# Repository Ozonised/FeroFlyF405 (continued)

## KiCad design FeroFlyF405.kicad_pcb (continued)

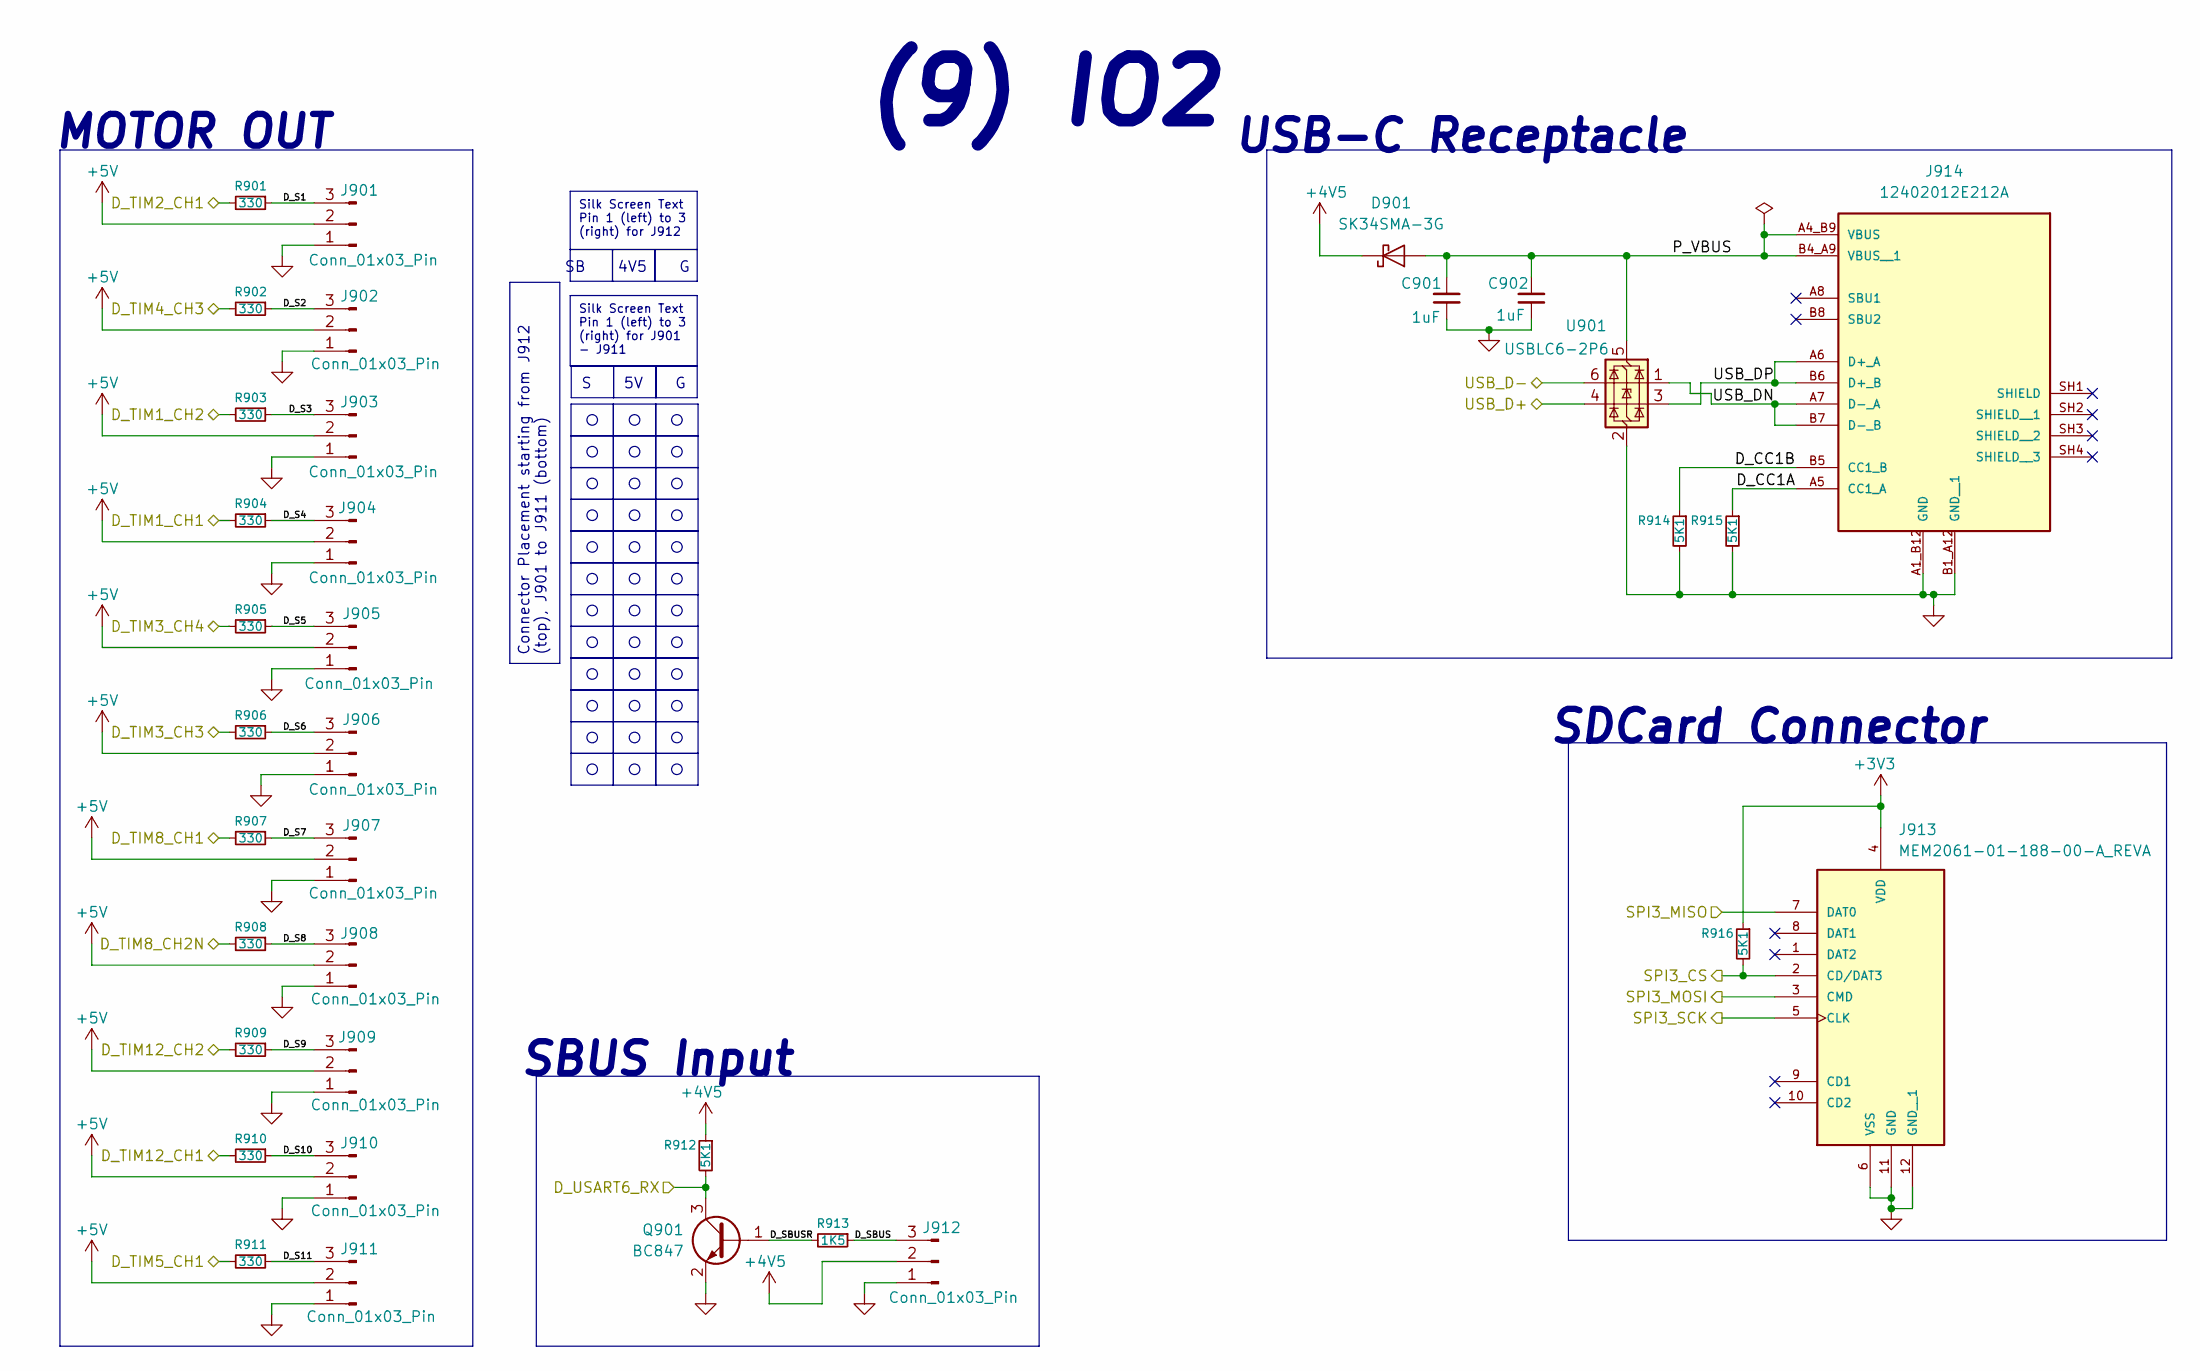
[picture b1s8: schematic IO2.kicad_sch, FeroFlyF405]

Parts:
C901, C902: 1uF; C_0603_1608Metric_Pad1.08x0.95mm_HandSolder; MPN C1608X7R1V105K080AC
D901: SK34SMA-3G; D_SMA; MPN SK34SMA-3G
J901, J902, J903, J904, J905, J906, J907, J908, J909, J910, J911, J912: Conn_01x03_Pin; PinHeader_1x03_P2.54mm_Vertical
J913: MEM2061-01-188-00-A_REVA; GCT_MEM2061-01-188-00-A_REVA
J914: 12402012E212A; AMPHENOL_12402012E212A; PARTREV 4
Q901: BC847; SOT-23; MPN BC847
R901, R902, R903, R904, R905, R906, R907, R908, R909, R910, R911: 330; R_0603_1608Metric_Pad0.98x0.95mm_HandSolder; MPN CR0603-FX-3300ELF
R912, R914, R915, R916: 5K1; R_0603_1608Metric_Pad0.98x0.95mm_HandSolder; MPN CR0603-FX-5101ELF
R913: 1K5; R_0603_1608Metric_Pad0.98x0.95mm_HandSolder; MPN CR0603-FX-3300ELF
U901: USBLC6-2P6; SOT-666; MPN USBLC6-2P6

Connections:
+3V3: J913.4 (VDD), R916.1; also elsewhere on the board
+4V5: D901.1 (K), J912.2, R912.1; also elsewhere on the board
+5V: J901.2, J902.2, J903.2, J904.2, J905.2, J906.2, J907.2, J908.2, J909.2, J910.2, J911.2; also elsewhere on the board
/IO/D_TIM1_CH1: R904.2; also elsewhere on the board
/IO/D_TIM1_CH2: R903.2; also elsewhere on the board
/IO/D_TIM2_CH1: R901.2; also elsewhere on the board
/IO/D_TIM3_CH3: R906.2; also elsewhere on the board
/IO/D_TIM3_CH4: R905.2; also elsewhere on the board
/IO/D_TIM4_CH3: R902.2; also elsewhere on the board
/IO/D_TIM5_CH1: R911.2; also elsewhere on the board
/IO/D_TIM8_CH1: R907.2; also elsewhere on the board
/IO/D_TIM8_CH2N: R908.2; also elsewhere on the board
/IO/D_TIM12_CH1: R910.2; also elsewhere on the board
/IO/D_TIM12_CH2: R909.2; also elsewhere on the board
/IO/D_USART6_RX: Q901.3 (C), R912.2; also elsewhere on the board
/IO/IO2/D_CC1A: J914.A5 (CC1_A), R915.1
/IO/IO2/D_CC1B: J914.B5 (CC1_B), R914.1
/IO/IO2/D_S1: J901.3, R901.1
/IO/IO2/D_S2: J902.3, R902.1
/IO/IO2/D_S3: J903.3, R903.1
/IO/IO2/D_S4: J904.3, R904.1
/IO/IO2/D_S5: J905.3, R905.1
/IO/IO2/D_S6: J906.3, R906.1
/IO/IO2/D_S7: J907.3, R907.1
/IO/IO2/D_S8: J908.3, R908.1
/IO/IO2/D_S9: J909.3, R909.1
/IO/IO2/D_S10: J910.3, R910.1
/IO/IO2/D_S11: J911.3, R911.1
/IO/IO2/D_SBUS: J912.3, R913.1
/IO/IO2/D_SBUSR: Q901.1 (B), R913.2
/IO/IO2/P_VBUS: C901.1, C902.1, D901.2 (A), J914.A4_B9 (VBUS), J914.B4_A9 (VBUS__1), U901.5 (VBUS)
/IO/IO2/USB_DN: J914.A7 (D-_A), J914.B7 (D-_B), U901.1 (I/O1)
/IO/IO2/USB_DP: J914.A6 (D+_A), J914.B6 (D+_B), U901.3 (I/O2)
/IO/SPI3_CS: J913.2 (CD/DAT3), R916.2; also elsewhere on the board
/IO/SPI3_MISO: J913.7 (DAT0); also elsewhere on the board
/IO/SPI3_MOSI: J913.3 (CMD); also elsewhere on the board
/IO/SPI3_SCK: J913.5 (CLK); also elsewhere on the board
/IO/USB_D+: U901.4 (I/O2); also elsewhere on the board
/IO/USB_D-: U901.6 (I/O1); also elsewhere on the board
GND: C901.2, C902.2, J901.1, J902.1, J903.1, J904.1, J905.1, J906.1, J907.1, J908.1, J909.1, J910.1, J911.1, J912.1, J913.6 (VSS), J913.11 (GND), J913.12 (GND__1), J914.A1_B12 (GND), J914.B1_A12 (GND__1), Q901.2 (E), R914.2, R915.2, U901.2 (GND); also elsewhere on the board

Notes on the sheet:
MOTOR OUT
S 5V G
USB-C Receptacle
SDCard Connector
SBUS Input
SB 4V5 G
(9) IO2
Silk Screen Text Pin 1 (left) to 3 (right) for J912
Silk Screen Text Pin 1 (left) to 3 (right) for J901 - J911
Connector Placement starting from J912 (top), J901 to J911 (bottom)

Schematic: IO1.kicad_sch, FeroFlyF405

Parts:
C801, C803, C805: 2.2uF; C_0805_2012Metric; MPN GCM21BR71C225KA64L
C802: 1uF; C_0603_1608Metric_Pad1.08x0.95mm_HandSolder; MPN C1608X7R1V105K080AC
C804: 0.1uF; C_0603_1608Metric_Pad1.08x0.95mm_HandSolder; MPN C1608X5R1H104K080AA
J801, J805: SM06B-GHS-TB(LF)(SN); JST_GH_SM06B-GHS-TB_1x06-1MP_P1.25mm_Horizontal; MPN JST_GH_SM06B-GHS-TB
J802, J804: SM04B-GHS-TB(LF)(SN); JST_GH_SM04B-GHS-TB_1x04-1MP_P1.25mm_Horizontal; MPN SM04B-GHS-TB(LF)(SN)
J803: SM03B-GHS-TB(LF)(SN); JST_GH_SM03B-GHS-TB_1x03-1MP_P1.25mm_Horizontal; MPN SM03B-GHS-TB(LF)(SN)
J806: Conn_01x02_MountingPin; Hirose_DF13C_CL535-0402-2-51_1x02-1MP_P1.25mm_Vertical
Q801: BC847; SOT-23; MPN BC847
R801: 10K; R_0603_1608Metric_Pad0.98x0.95mm_HandSolder; MPN CR0603-FX-1002ELF
R803: 1K5; R_0603_1608Metric_Pad0.98x0.95mm_HandSolder; MPN CR0603-FX-3300ELF
TP801, TP802, TP803, TP804, TP805, TP806, TP807, TP808, TP809, TP810, TP811, TP812, TP813, TP814, TP815, TP816: TestPoint; TestPoint_Pad_1.0x1.0mm

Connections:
+4V5: C801.1, C802.1, C803.1, J801.1, J802.1, J804.1, TP801.1 (1_1), TP802.1 (1_1); also elsewhere on the board
+5V: C805.1, J803.1, J805.1, J806.1, TP811.1 (1_1), TP815.1 (1_1); also elsewhere on the board
/IO/D_ADC1_CH10: C804.1, R801.1; also elsewhere on the board
/IO/D_BUZZER: R803.1; also elsewhere on the board
/IO/D_I2C1_SCL: J801.4, J804.2, TP806.1 (1_1); also elsewhere on the board
/IO/D_I2C1_SDA: J801.5, J804.3, TP810.1 (1_1); also elsewhere on the board
/IO/D_USART2_RX: J805.3, TP813.1 (1_1); also elsewhere on the board
/IO/D_USART2_TX: J805.2, TP812.1 (1_1); also elsewhere on the board
/IO/D_USART4_RX: J802.3, TP807.1 (1_1); also elsewhere on the board
/IO/D_USART4_TX: J802.2, TP804.1 (1_1); also elsewhere on the board
/IO/D_USART5_RX: J801.3, TP805.1 (1_1); also elsewhere on the board
/IO/D_USART5_TX: J801.2, TP803.1 (1_1); also elsewhere on the board
/IO/IO1/D_BUZ-: J806.2, Q801.3 (C), TP816.1 (1_1)
/IO/IO1/D_BUZR: Q801.1 (B), R803.2
/IO/IO1/D_CUR: J803.3, R801.2
GND: C801.2, C802.2, C803.2, C804.2, C805.2, J801.6, J802.4, J803.2, J804.4, J805.6, Q801.2 (E), TP808.1 (1_1), TP809.1 (1_1), TP814.1 (1_1); also elsewhere on the board

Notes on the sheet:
Telemetry Port
I2C1 Port
BUZZER
RC Receiver
(8) IO1
GPS Port
CURRENT SENSOR
Current input voltage: 3V3 max Cut off freq: 159 Hz Place away from switching circuits
SILK SCREEN TEXT GUIDELINE

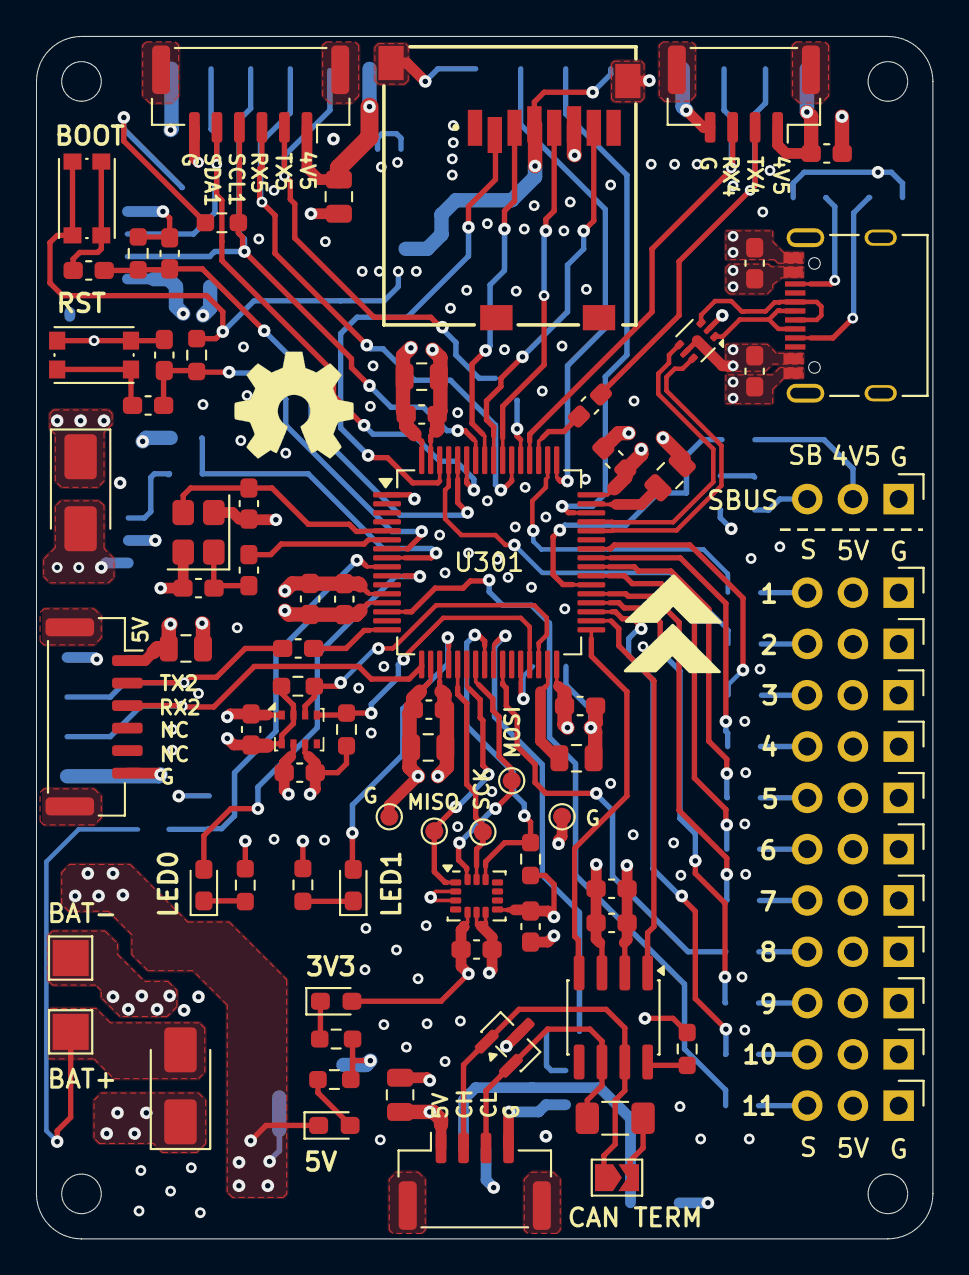
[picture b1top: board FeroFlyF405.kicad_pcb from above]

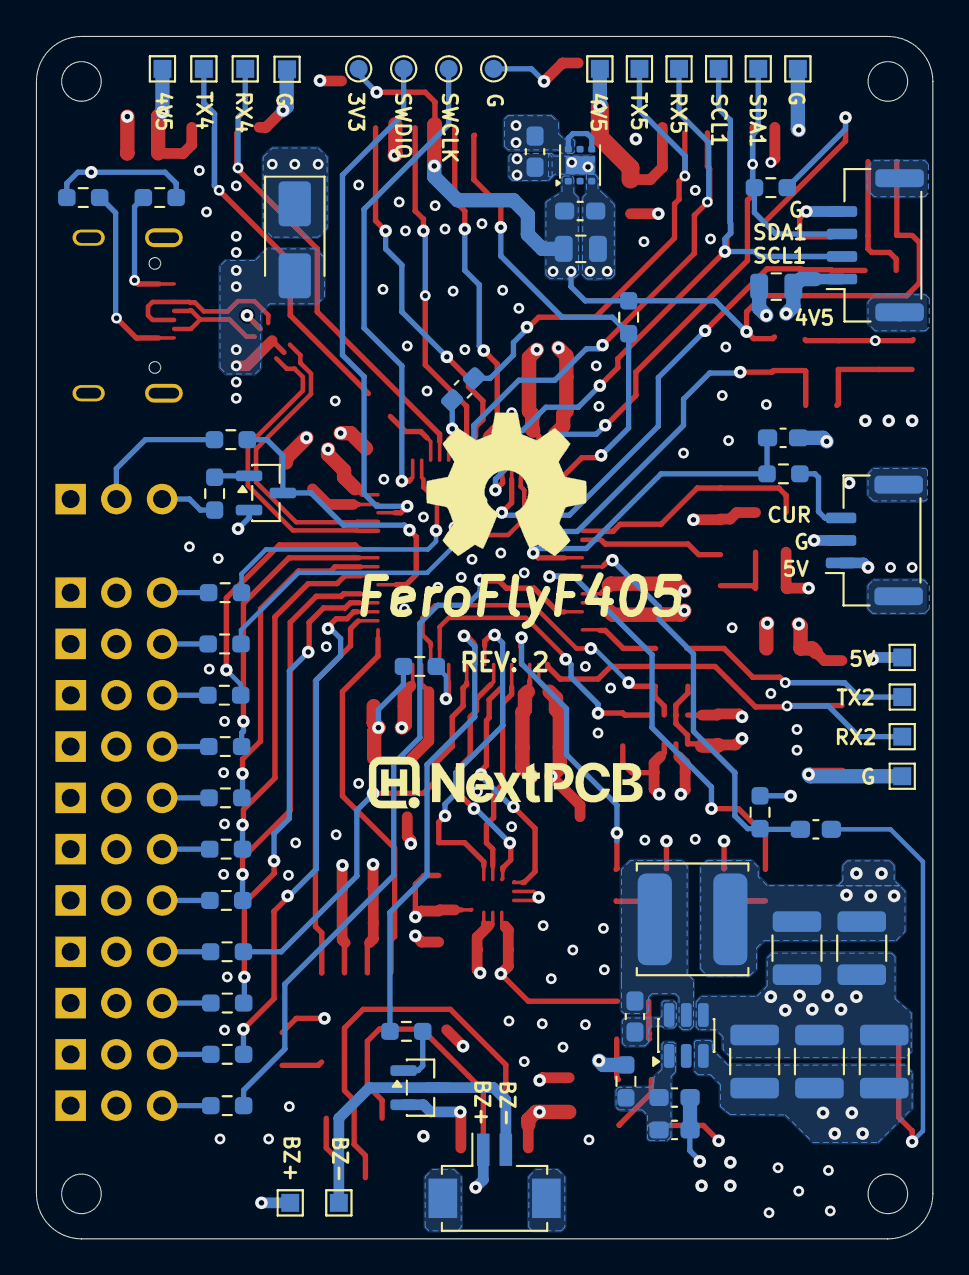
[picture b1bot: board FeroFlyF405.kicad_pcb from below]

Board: 4 copper layers, 49.8 x 66.8 mm, 154 parts (66 on the bottom side), 92 nets.

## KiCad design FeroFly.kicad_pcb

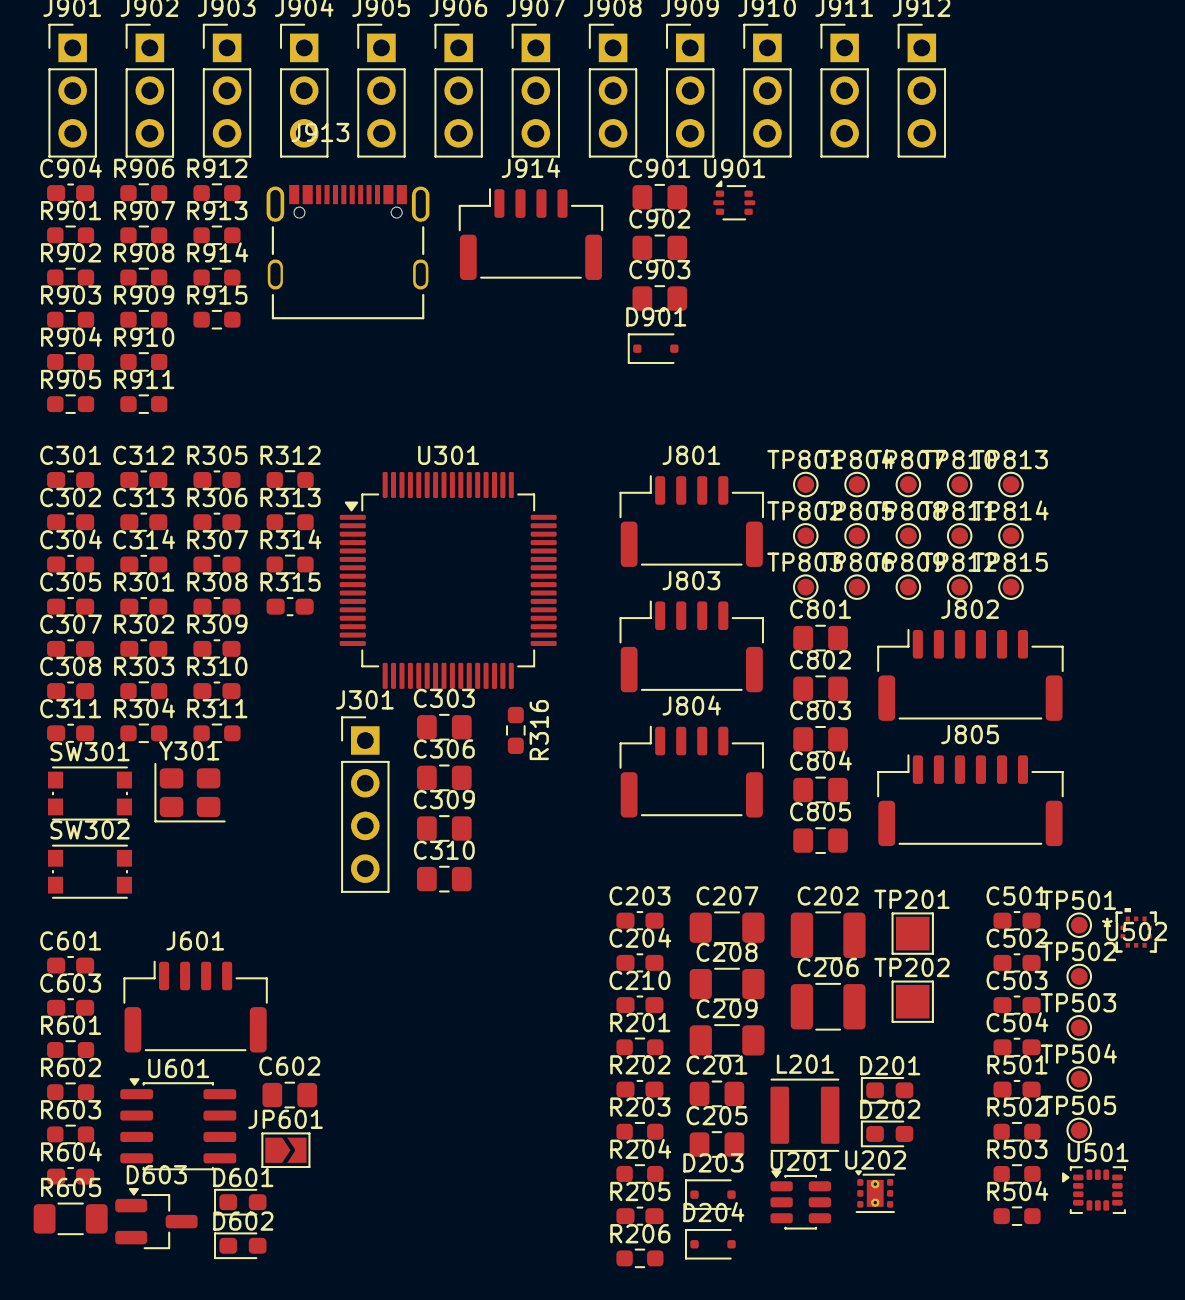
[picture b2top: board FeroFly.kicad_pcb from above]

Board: 2 copper layers, 153 parts (0 on the bottom side), 91 nets, no tracks yet.

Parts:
C201, C303, C306, C309, C310, C602, C801, C802, C803, C804, C805, C901, C902, C903: 2.2uF; C_0805_2012Metric_Pad1.18x1.45mm_HandSolder
C202, C206: 22uF; C_1210_3225Metric_Pad1.33x2.70mm_HandSolder
C203, C204, C314, C603: 1uF; C_0603_1608Metric_Pad1.08x0.95mm_HandSolder
C205: 330nF; C_0805_2012Metric_Pad1.18x1.45mm_HandSolder
C207, C208, C209: 10uF; C_1206_3216Metric_Pad1.33x1.80mm_HandSolder
C210, C301, C302, C307, C308, C311, C312, C313, C501, C502, C503, C504, C601, C904: 0.1uF; C_0603_1608Metric_Pad1.08x0.95mm_HandSolder
C304, C305: 18pF; C_0603_1608Metric_Pad1.08x0.95mm_HandSolder
D201, D202, D601, D602: LTST-C190KRKT; LED_0603_1608Metric_Pad1.05x0.95mm_HandSolder
D203, D204, D901: PMEG3020EJ; D_SOD-323F
D603: ESDCAN01-2BLY; SOT-23_Handsoldering
H101, H102, H103, H104: MountingHole; MountingHole_3.2mm_M3
J301: Conn_01x04_Pin; PinHeader_1x04_P2.54mm_Vertical
J601, J801, J803, J804, J914: SM04B-GHS-TB(LF)(SN); JST_GH_SM04B-GHS-TB_1x04-1MP_P1.25mm_Horizontal
J802, J805: SM06B-GHS-TB(LF)(SN); JST_GH_SM06B-GHS-TB_1x06-1MP_P1.25mm_Horizontal
J901, J902, J903, J904, J905, J906, J907, J908, J909, J910, J911, J912: Conn_01x03_Pin; PinHeader_1x03_P2.54mm_Vertical
J913: 12402012E212A; AMPHENOL_12402012E212A
JP601: Jumper; SolderJumper-2_P1.3mm_Open_TrianglePad1.0x1.5mm
L201: 4.7uH; L_Abracon_ASPI-4030S
R201, R204, R601, R602, R904, R905, R906, R907, R908, R909, R910, R911, R912, R913, R914, R915: 330; R_0603_1608Metric_Pad0.98x0.95mm_HandSolder
R202, R205: 52K3; C_0603_1608Metric_Pad1.08x0.95mm_HandSolder
R203, R206, R316, R603, R903: 10K; R_0603_1608Metric_Pad0.98x0.95mm_HandSolder
R301, R302, R305, R306, R307, R308, R309, R310, R315, R501, R604: 22; C_0603_1608Metric_Pad1.08x0.95mm_HandSolder
R303, R304, R311, R312, R313, R314, R502, R503, R504, R901, R902: 5K1; R_0603_1608Metric_Pad0.98x0.95mm_HandSolder
R605: 120; R_1206_3216Metric_Pad1.30x1.75mm_HandSolder
SW301, SW302: SW_Push; SW_Push_1P1T_NO_CK_KMR2
TP201, TP202: TestPoint; TestPoint_Pad_2.0x2.0mm
TP501, TP502, TP503, TP504, TP505, TP801, TP802, TP803, TP804, TP805, TP806, TP807, TP808, TP809, TP810, TP811, TP812, TP813, TP814, TP815: TestPoint; TestPoint_Pad_D1.0mm
U201: AP62200WU-7; TSOT-23-6
U202: TLV75733PDRV; WSON-6-1EP_2x2mm_P0.65mm_EP1x1.6mm_ThermalVias
U301: STM32F405RGTx; LQFP-64_10x10mm_P0.5mm
U501: LSM6DSL; LGA-14_3x2.5mm_P0.5mm_LayoutBorder3x4y
U502: BMP390; 10LGA_2X2X0p75_BOS
U601: SN65HVD230DR; SOIC-8_3.9x4.9mm_P1.27mm
U901: USBLC6-2P6; SOT-666
Y301: 24MHz; Crystal_SMD_3225-4Pin_3.2x2.5mm

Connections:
+3V3: C201.1, C203.1, C303.1, C306.1, C307.1, C308.1, C311.1, C312.1, C313.1, C314.1, C501.1, C502.1, C503.1, C504.1, C601.1, C603.1, D201.2 (A), J301.1, R303.1, R311.1, R312.1, R313.1, R314.1, R502.1, R503.1, R504.1, SW302.1, U202.1 (OUT), U301.1 (VBAT), U301.13 (VDDA), U301.19 (VDD), U301.32 (VDD), U301.48 (VDD), U301.64 (VDD), U501.5 (VDDIO), U501.8 (VDD), U502.1 (VDDIO), U502.6 (CSB), U502.10 (VDD), U601.3 (VCC)
+5V: C202.1, C206.1, C602.1, C801.1, C802.1, C803.1, C804.1, C805.1, C903.1, D202.1 (K), D204.2 (A), J601.1, J801.1, J802.1, J803.1, J804.1, J805.1, J901.2, J902.2, J903.2, J904.2, J905.2, J906.2, J907.2, J908.2, J909.2, J910.2, J911.2, J912.2, J914.1, L201.2, R202.1
/IO/D_ADC2_CH12: C904.1, R903.1, U301.10 (PC2)
/IO/D_I2C1_SCL: J802.4, J803.2, R312.2, R314.2, TP803.1 (1_1), U301.58 (PB6)
/IO/D_I2C1_SDA: J802.5, J803.3, R311.2, R313.2, TP801.1 (1_1), U301.59 (PB7)
/IO/D_PINIO0: J804.2, TP810.1 (1_1), U301.56 (PB4)
/IO/D_PINIO1: J804.3, TP811.1 (1_1), U301.57 (PB5)
/IO/D_TIM1_CH1: R907.2, U301.41 (PA8)
/IO/D_TIM1_CH2: R906.2, U301.42 (PA9)
/IO/D_TIM2_CH1: R912.2, U301.14 (PA0)
/IO/D_TIM3_CH3: R909.2, U301.39 (PC8)
/IO/D_TIM3_CH4: R908.2, U301.40 (PC9)
/IO/D_TIM4_CH3: R904.2, U301.61 (PB8)
/IO/D_TIM4_CH4: R905.2, U301.62 (PB9)
/IO/D_TIM5_CH1: R915.2, U301.15 (PA1)
/IO/D_TIM8_CH1: R911.2, U301.37 (PC6)
/IO/D_TIM8_CH2: R910.2, U301.38 (PC7)
/IO/D_TIM12_CH1: R914.2, U301.35 (PB14)
/IO/D_TIM12_CH2: R913.2, U301.36 (PB15)
/IO/D_USART2_RX: J805.3, TP805.1 (1_1), U301.17 (PA3)
/IO/D_USART2_TX: J805.2, R308.1, TP804.1 (1_1)
/IO/D_USART4_RX: J801.3, TP808.1 (1_1), U301.52 (PC11)
/IO/D_USART4_TX: J801.2, R306.2, TP807.1 (1_1)
/IO/D_USART5_RX: J802.3, TP814.1 (1_1), U301.54 (PD2)
/IO/D_USART5_TX: J802.2, R307.2, TP813.1 (1_1)
/IO/IO2/D_CC1A: J913.A5 (CC1_A), R901.1
/IO/IO2/D_CC1B: J913.B5 (CC1_B), R902.1
/IO/IO2/D_CUR: J914.3, R903.2
/IO/IO2/D_S1: J901.3, R904.1
/IO/IO2/D_S2: J902.3, R905.1
/IO/IO2/D_S3: J903.3, R906.1
/IO/IO2/D_S4: J904.3, R907.1
/IO/IO2/D_S5: J905.3, R908.1
/IO/IO2/D_S6: J906.3, R909.1
/IO/IO2/D_S7: J907.3, R910.1
/IO/IO2/D_S8: J908.3, R911.1
/IO/IO2/D_S9: J909.3, R912.1
/IO/IO2/D_S10: J910.3, R913.1
/IO/IO2/D_S11: J911.3, R914.1
/IO/IO2/D_S12: J912.3, R915.1
/IO/IO2/P_VBUS: C901.1, C902.1, D901.2 (A), J913.A4_B9 (VBUS), J913.B4_A9 (VBUS__1), U901.5 (VBUS)
/IO/IO2/USB_DN: J913.A7 (D-_A), J913.B7 (D-_B), U901.1 (I/O1)
/IO/IO2/USB_DP: J913.A6 (D+_A), J913.B6 (D+_B), U901.3 (I/O2)
/IO/P_LDOIN: C204.1, D204.1 (K), D901.1 (K), U202.4 (EN), U202.6 (IN)
/IO/USB_D+: U301.44 (PA11), U901.4 (I/O2)
/IO/USB_D-: U301.45 (PA12), U901.6 (I/O1)
/MCU/D_ADC1_CH11: C210.1, R205.2, R206.1, U301.9 (PC1)
/MCU/D_BOOT0: C302.1, R302.1, R304.1, U301.60 (BOOT0)
/MCU/D_BOOT0R: R302.2, SW302.2
/MCU/D_BOOT1: R316.1, U301.28 (PB2)
/MCU/D_CAN2RX: R604.2, U301.33 (PB12)
/MCU/D_CAN2TX: R315.1, U601.1 (D)
/MCU/D_CAN2TXR: R315.2, U301.34 (PB13)
/MCU/D_I2C2_SCL: R504.2, U301.29 (PB10), U502.2 (SCK)
/MCU/D_I2C2_SDA: R503.2, U301.30 (PB11), U502.4 (SDI)
/MCU/D_LED0: D601.2 (A), U301.26 (PB0)
/MCU/D_LED1: D602.2 (A), U301.27 (PB1)
/MCU/D_NRST: C301.1, R301.1, R303.2, U301.7 (NRST)
/MCU/D_NRSTR: R301.2, SW301.2
/MCU/D_OSC_IN: C304.1, U301.5 (PH0), Y301.3
/MCU/D_OSC_OUT: R305.1, U301.6 (PH1)
/MCU/D_OSC_OUTR: C305.2, R305.2, Y301.1
/MCU/D_PA2: R308.2, U301.16 (PA2)
/MCU/D_PA5: R309.2, U301.21 (PA5)
/MCU/D_PA7: R310.2, U301.23 (PA7)
/MCU/D_PC10: R306.1, U301.51 (PC10)
/MCU/D_PC12: R307.1, U301.53 (PC12)
/MCU/D_SPI1_CS: R502.2, TP504.1 (1_1), U301.24 (PC4), U501.12 (CS)
/MCU/D_SPI1_MISO: R501.2, TP501.1 (1_1), U301.22 (PA6)
/MCU/D_SPI1_MOSI: R310.1, TP502.1 (1_1), U501.14 (SDA)
/MCU/D_SPI1_SCK: R309.1, TP503.1 (1_1), U501.13 (SCL)
/MCU/D_SWCLK: J301.3, U301.49 (PA14)
/MCU/D_SWDIO: J301.2, U301.46 (PA13)
/MCU/P_VCAP1: C309.1, U301.31 (VCAP_1)
/MCU/P_VCAP2: C310.1, U301.47 (VCAP_2)
/Peripherals/CAN & LEDs/CAN+: D603.2 (K), J601.2, JP601.1 (A), U601.7 (CANH)
/Peripherals/CAN & LEDs/CAN-: D603.1 (K), J601.3, R605.2, U601.6 (CANL)
/Peripherals/CAN & LEDs/D_CANR: R604.1, U601.4 (R)
/Peripherals/CAN & LEDs/D_R_LED0: D601.1 (K), R601.2
/Peripherals/CAN & LEDs/D_R_LED1: D602.1 (K), R602.2
/Peripherals/IMUs/D_SPI1_MISOR: R501.1, U501.1 (SDO/SA0)
/Power/D_FB: R202.2, R203.1, U201.4 (FB)
/Power/P_SW: C205.1, L201.1, U201.2 (SW)
/Power/P_VIN: D203.2 (A), TP201.1 (1_1)
GND: C201.2, C202.2, C203.2, C204.2, C206.2, C207.2, C208.2, C209.2, C210.2, C301.2, C302.2, C303.2, C304.2, C305.1, C306.2, C307.2, C308.2, C309.2, C310.2, C311.2, C312.2, C313.2, C314.2, C501.2, C502.2, C503.2, C504.2, C601.2, C602.2, C603.2, C801.2, C802.2, C803.2, C804.2, C805.2, C901.2, C902.2, C903.2, C904.2, D603.3 (A), J301.4, J601.4, J601.MP (MountPin), J801.4, J801.MP (MountPin), J802.6, J802.MP (MountPin), J803.4, J803.MP (MountPin), J804.4, J804.MP (MountPin), J805.6, J805.MP (MountPin), J901.1, J902.1, J903.1, J904.1, J905.1, J906.1, J907.1, J908.1, J909.1, J910.1, J911.1, J912.1, J913.A1_B12 (GND), J913.B1_A12 (GND__1), J914.2, J914.4, J914.MP (MountPin), R201.2, R203.2, R204.2, R206.2, R304.2, R316.2, R601.1, R602.1, R603.2, R901.2, R902.2, SW301.1, TP202.1 (1_1), TP505.1 (1_1), TP802.1 (1_1), TP806.1 (1_1), TP809.1 (1_1), TP812.1 (1_1), TP815.1 (1_1), U201.1 (GND), U202.3 (GND), U202.7 (GND), U301.12 (VSSA), U301.18 (VSS), U301.63 (VSS), U501.2 (SDX), U501.3 (SCX), U501.6 (GND), U501.7 (GND), U502.3 (VSS), U502.5 (SDO), U502.8 (VSS), U502.9 (VSS), U601.2 (GND), U901.2 (GND), Y301.2 (G), Y301.4 (G)
unnamed: D201.1 (K), R201.1
unnamed: D202.2 (A), R204.1
unnamed: JP601.2 (B), R605.1
unnamed: C205.2, U201.6 (BST)
unnamed: R603.1, U601.8 (Rs)
VBAT: C207.1, C208.1, C209.1, D203.1 (K), R205.1, U201.3 (IN)
